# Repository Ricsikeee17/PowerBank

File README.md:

\# Custom PowerBank

This is a custom made powerbank from scratch that will use 18650 batteries from a laptop battery.

\##PCB

I made the PCB with KiCAD and here's some screenshot of the schematic and the PCB:

\##CAD Model

The CAD model was made in Shapr3D it's fully 3D printable. It's only 2 parts and I think I will glue the together when assembling it.

A screenshot:

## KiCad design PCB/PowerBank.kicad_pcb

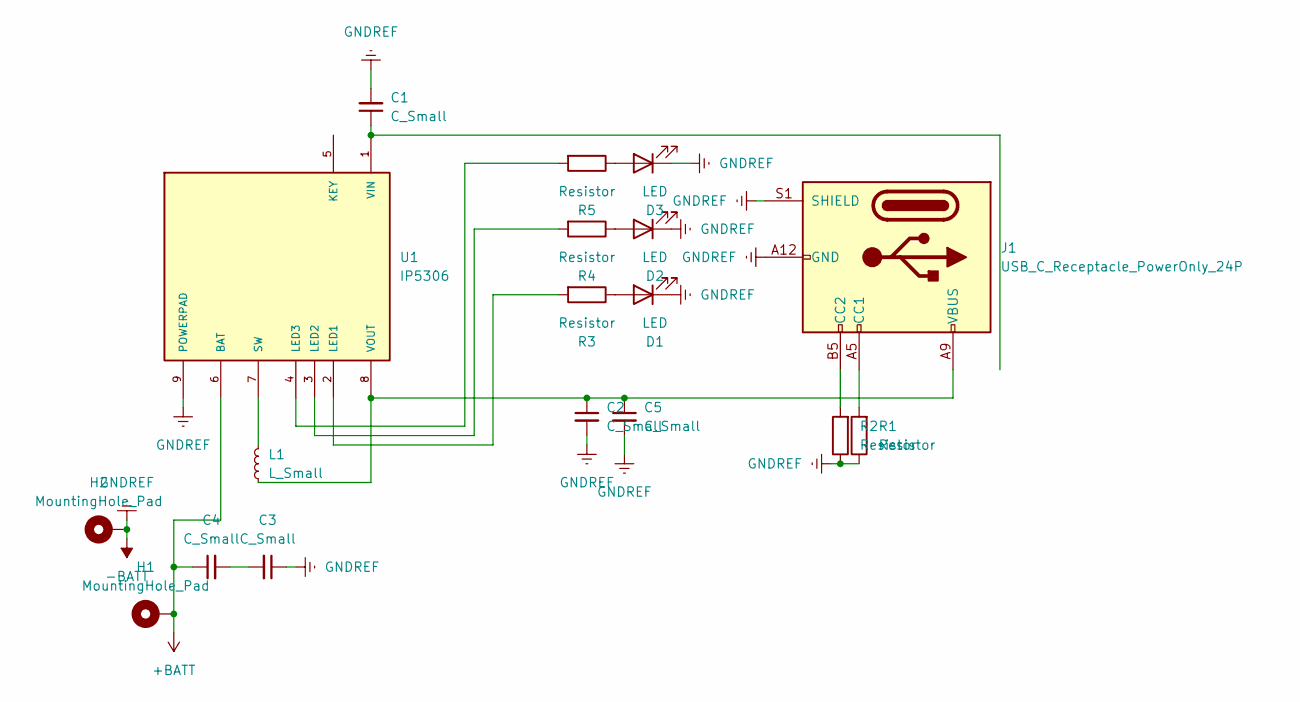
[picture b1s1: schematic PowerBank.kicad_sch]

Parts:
C1, C2, C3, C4, C5: C_Small; C_0805_2012Metric
D1, D2, D3: LED; LED_1206_3216Metric
H1: MountingHole_Pad; BATT+_MOUNTING_HOLE
H2: MountingHole_Pad; BATT-_MOUNTING_HOLE
J1: USB_C_Receptacle_PowerOnly_24P; USB_C_Receptacle_Amphenol_12401610E4-2A_CircularHoles
L1: L_Small; L_Vishay_IHLP-1616
R1, R2, R3, R4, R5: Resistor; R_0805_2012Metric
U1: IP5306; SOP127P600X165-9N; PARTREV 1.31

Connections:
+BATT: C4.1, H1.1, U1.6 (BAT)
-BATT: C1.2, C2.2, C3.1, C5.2, D1.1 (K), D2.1 (K), D3.1 (K), H2.1, J1.A1 (GND), J1.A12 (GND), J1.B1 (GND), J1.B12 (GND), J1.S1 (SHIELD), R1.1, R2.1, U1.9 (POWERPAD)
unnamed: C3.2, C4.2
unnamed: D1.2 (A), R3.1
unnamed: D2.2 (A), R4.1
unnamed: D3.2 (A), R5.1
unnamed: J1.A5 (CC1), R1.2
unnamed: J1.B5 (CC2), R2.2
unnamed: R3.2, U1.2 (LED1)
unnamed: R4.2, U1.3 (LED2)
unnamed: R5.2, U1.4 (LED3)
unnamed: L1.2, U1.7 (SW)
unnamed: C1.1, U1.1 (VIN)
unnamed: C2.1, C5.1, J1.A4 (VBUS), J1.A9 (VBUS), J1.B4 (VBUS), J1.B9 (VBUS), L1.1, U1.8 (VOUT)

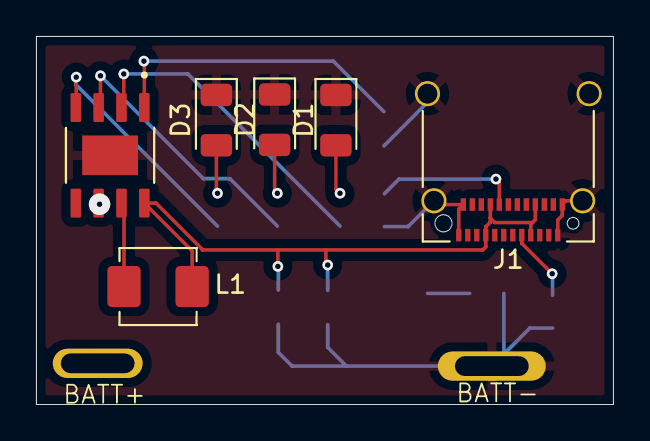
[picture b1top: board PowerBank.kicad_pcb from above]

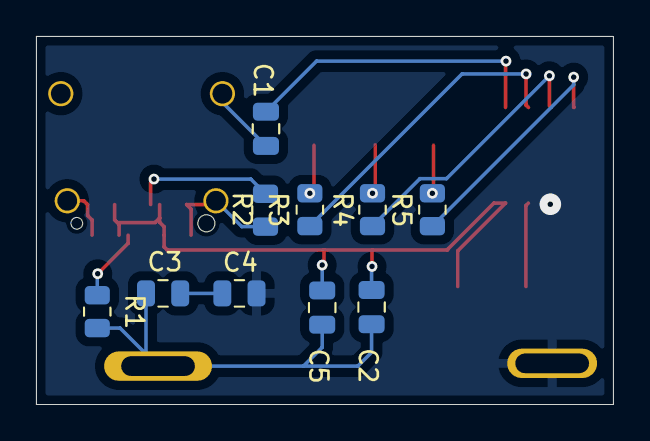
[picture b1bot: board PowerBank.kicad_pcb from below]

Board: 2 copper layers, 32.1 x 20.4 mm, 18 parts (10 on the bottom side), 14 nets.

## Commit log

2026-03-28 Production folder
